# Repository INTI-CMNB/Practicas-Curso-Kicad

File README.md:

# Practicas-Curso-Kicad
Prácticas para el curso Introductorio de de Kicad dictado por INTI.

## Consigna
Cada participante del curso trabajará en un subdirectorio con su Apellido_Nombre, sin espacios, tildes, eñes o caracteres especiales.

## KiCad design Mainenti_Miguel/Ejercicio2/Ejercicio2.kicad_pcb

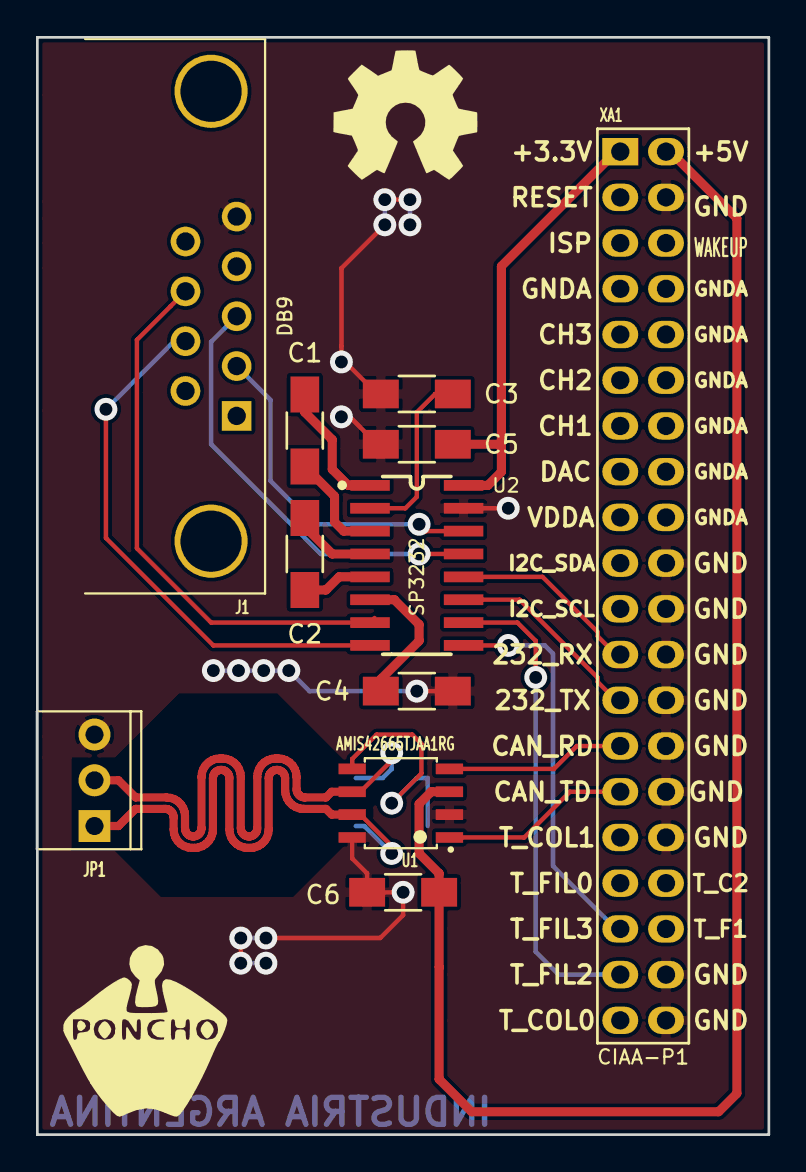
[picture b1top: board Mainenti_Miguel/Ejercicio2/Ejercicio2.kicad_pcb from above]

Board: 2 copper layers, 40.6 x 61.0 mm, 14 parts (0 on the bottom side), 22 nets.

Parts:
C1, C2, C3, C4, C5: 100nF; C_1206_Handsoldering
C6: C; C_1206_Handsoldering
G101: Logo_OSHWA
J1: DB9; DB9_F_TH
JP1: CONN_3; CON_PALETA_3
R1, R2: 60; R_1206_HandSoldering
U1: AMIS42665TJAA1RG; SOIC-8
U2: SP3232; SP3232ECN-SOIC16N
XA1: Conn_Poncho2P_2x_20x2; Conn_Poncho_Derecha

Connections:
+3.3V: C5.1, U2.16, XA1.1
+5V: C6.2, U1.3, XA1.2
/Conector y Can/CAN_N: JP1.2, R2.2, U1.6
/Conector y Can/CAN_P: JP1.1, R1.1, U1.7
/Conector y Can/CAN_RX: U1.4, XA1.27
/Conector y Can/CAN_TX: U1.1, XA1.29
/Conector y Can/CTS: U2.10, XA1.37
/Conector y Can/RTS: U2.9, XA1.35
/Conector y Can/RXD: U2.11, XA1.25
/Conector y Can/TXD: U2.12, XA1.23
GND: C3.1, C4.1, C5.2, C6.1, J1.5, JP1.3, U1.2, U1.8, U2.15, XA1.4, XA1.20, XA1.22, XA1.24, XA1.26, XA1.28, XA1.30, XA1.32, XA1.38, XA1.40
unnamed: C1.1, U2.1
unnamed: C1.2, U2.3
unnamed: C2.1, U2.4
unnamed: C2.2, U2.5
unnamed: C3.2, U2.2
unnamed: C4.2, U2.6
unnamed: J1.2, U2.14
unnamed: J1.3, U2.13
unnamed: J1.7, U2.8
unnamed: J1.8, U2.7
unnamed: R1.2, R2.1, U1.5

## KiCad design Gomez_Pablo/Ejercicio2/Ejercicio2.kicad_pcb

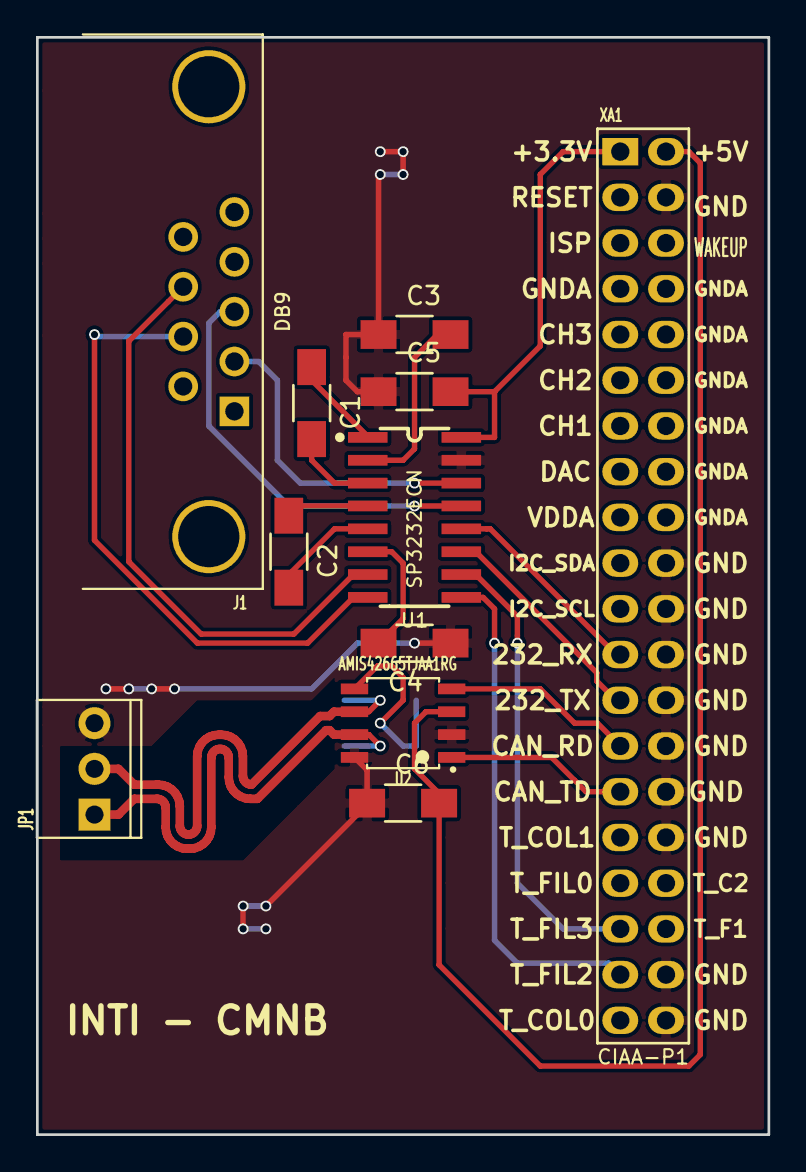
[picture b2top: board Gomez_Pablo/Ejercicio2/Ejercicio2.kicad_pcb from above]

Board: 2 copper layers, 40.6 x 61.0 mm, 13 parts (0 on the bottom side), 22 nets.

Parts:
C1, C2, C3, C4, C5: 100nF; C_1206_Handsoldering
C6: 100 nF; C_1206_Handsoldering
J1: DB9; DB9_F_TH
JP1: CAN; CON_PALETA_3
R1, R2: 60; R_1206_HandSoldering
U1: SP3232ECN; SP3232ECN-SOIC16N
U2: AMIS42665TJAA1RG; SOIC-8
XA1: Conn_Poncho2P_2x_20x2; Conn_Poncho_Derecha

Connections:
+3.3V: C5.2, U1.16, XA1.1
+5V: C6.2, U2.3, XA1.2
/Conector/CAN_N: JP1.2, R2.2, U2.6
/Conector/CAN_P: JP1.1, R1.1, U2.7
/Conector/CAN_RX: U2.4, XA1.27
/Conector/CAN_TX: U2.1, XA1.29
/Conector/CTS: U1.10, XA1.35
/Conector/RTS: U1.9, XA1.37
/Conector/RXD: U1.11, XA1.25
/Conector/TXD: U1.12, XA1.23
GND: C3.1, C4.1, C5.1, C6.1, JP1.3, U1.15, U2.2, U2.8, XA1.4, XA1.20, XA1.22, XA1.24, XA1.26, XA1.28, XA1.30, XA1.32, XA1.38, XA1.40
unnamed: C1.1, U1.1
unnamed: C1.2, U1.3
unnamed: C2.1, U1.4
unnamed: C2.2, U1.5
unnamed: C3.2, U1.2
unnamed: C4.2, U1.6
unnamed: J1.2, U1.14
unnamed: J1.3, U1.13
unnamed: J1.7, U1.8
unnamed: J1.8, U1.7
unnamed: R1.2, R2.1, U2.5

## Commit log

2015-11-18 Creo directorio.
2015-11-19 Edito el README.
2015-11-26 pruebas sobre lista.
2015-11-26 Agrego UVAS.
2015-11-26 Agrego GUINDA.
2015-11-26 Borro lista de compras.
2015-11-27 Agregados los archivos para los ejercicios 1 y 2.
2015-11-27 Muevo dir Diego_Brengi a Materiales
2015-11-27 Agregados los directorios de trabajo de los asistentes.
2015-12-01 Agrego presentación Día 2.
2015-12-01 se cambio en el id
2015-12-01 EHS Agrego Ejercicio1
2015-12-01 Agrego mi ejercicio1
2015-12-01 Agrego mi ejercicio1.
2015-12-01 Agrego ejercicio 1
2015-12-01 Agrego mi ejercicio 1
2015-12-01 NS: Agrego mi ejercicio 1
2015-12-01 Agrego mi ejercicio 1. DC
2015-12-01 Agrego mi ejercicio 1. PO
2015-12-01 Agrego mi ejercicio 1 SN.
2015-12-01 Ejercicio1
2015-12-01 Agrego ejercicio 1 1.0
2015-12-01 agrego el ejc1 version 1.0
2015-12-01 Agrego mi ejercicio 1.
2015-12-01 Agrego ej_1 ss
2015-12-01 ejercicio 1
2015-12-01 borrado
2015-12-01 Agrego Ej 1.
2015-12-01 Agrego ej. 1 final
2015-12-01 GoCu .Agrego ejercicio 1
2015-12-01 Borro carpeta vieja
2015-12-01 Añado nuevo directorio con Gerbers
2015-12-01 lista de ignorados
2015-12-01 Agrego gitignore
2015-12-01 inicio del proyecto 2
2015-12-01 subir gitignore
2015-12-01 adherido el ignore
2015-12-01 git ignore
2015-12-01 Agrego archivos a ignorar
2015-12-01 Se agrego .gitignore
2015-12-01 se sube gitignore
2015-12-01 Se agrega el archivo .gitignore
2015-12-01 add git ignore
2015-12-01 GoCu agrego el gitignore
2015-12-01 agregado ignore
2015-12-01 Agrego tabla RS232 DTE DCE.
2015-12-01 Agregado Ejercicio 2
2015-12-01 Realizado el Electrical Rule Check. Corregidos Errores Se agregó campo Digikey/Mouser en todos los componentes Se modificó Digikey/Mouser en U1 y U2
2015-12-01 Creado Netlist Realizado BOM con Scripts Python dentro de Kicad
2015-12-01 Added footprint library Assigned Foot-Symbol updated netlist and BOM
2015-12-01 Creado el Footprint 1206
2015-12-01 Cambiados footprints Revisando placement en PCB
2015-12-01 Agregado la presentación del día 1.
2015-12-02 mando archivos
2015-12-02 mi ejercicio2
2015-12-02 Minor changes on pcb
2015-12-02 ejercicio 2 pcb
2015-12-02 Se suben sólo los archivos recomendados
2015-12-02 GoCu subo el ruteo preliminar
2015-12-02 Se agregan los archivos opcionales
2015-12-02 Se sube Poncho_RS232_CAN_1.0.0
2015-12-02 Agrego archivos ej_2
2015-12-02 Agrego Ej2 solo ruteado sin planos
2015-12-02 Se agregan los directorios utilizados para el Ejercicio 2
2015-12-02 Agrego ej2 SN.
2015-12-02 agrego lo necesario
2015-12-02 change .gitignore
2015-12-02 GoCu modifico el gitignore
2015-12-02 Ejercicio 2
2015-12-02 Added GND planes
2015-12-02 Ejercicio 2 n
2015-12-02 Agrego .gitignore actualizado
2015-12-02 version 1 del poncho
2015-12-02 version 1 del poncho faltaba el conector.sch
2015-12-02 Faltan rutear GND
2015-12-02 Agrego los archivos del Ejercicio 2 con parte del PCB
2015-12-02 subo Ejercicio 2 1.1
2015-12-02 Agrego directorios del proyecto
2015-12-02 Subo Ejer2. PO
2015-12-02 sumado un archivo al gitignore
2015-12-02 actualizado
2015-12-02 Actualizo PCB
2015-12-02 agregadas leyendas, cutouts y keepouts
2015-12-02 Added 3D
2015-12-02 3D routing
2015-12-02 con 3d
2015-12-02 Agrego 3D
2015-12-02 Agrego 3d. PO
2015-12-02 Subo los 3d shapes
2015-12-02 Se sube la versión actualizada del pcb
2015-12-02 GoCu Agregado los planos y la vista 3D
2015-12-02 Se agregan los archivos pcb con 3d
2015-12-02 Se sube modelo 3d Poncho_RS232_CAN v1.0.0
2015-12-02 Version c/ modelos 3d
2015-12-02 se sube modificacion en pcb
2015-12-02 ruteado y con 3d
2015-12-02 Se sube 3dshapes
2015-12-02 Agregada Licencia
2015-12-02 Agrego licencia. PO
2015-12-02 licensia abierta
2015-12-02 Actualizo doc
2015-12-02 Agrego PCB ejercicio 2 con 3D SN
2015-12-02 se agregaron logos y licencia. Se activaron capas de cobre que estaban desactivadas
2015-12-02 plano de tierra y 3d
2015-12-02 Subo la licencia
2015-12-02 Se agrega modificacion de pcb y license
2015-12-02 modifico licencia
2015-12-02 nuevo componente
2015-12-02 Agrego componente multiparte. PO
2015-12-02 corregido
2015-12-02 se sube la librería modificada
2015-12-02 Se agrego libreria MP
2015-12-02 agrego libreria
2015-12-02 Actualizo carpeta libs
2015-12-02 Componente Multiparte
2015-12-02 IDEM
2015-12-02 se sube componente sp3232 multiparte
2015-12-02 agregado comp. multiparte
2015-12-02 GoCu Agregado el componente multipart
2015-12-02 agrego componente a ej2.lib
2015-12-02 change library
2015-12-02 lib mulitparte
2015-12-02 Agrego lib scp232 nueva esquematico SN
2015-12-02 Nuevo Footprint
2015-12-02 Agrego footprint smd 32 pines smd SN
2015-12-02 Se sube el footprint del QFN64 creado a partir del tutorial del CERN
2015-12-02 PCB Modo OpenGL
2015-12-02 Added Stack-UP
2015-12-02 Probada característica lenght tunning.
    Falló Kicad y no pude realizar el par diferencial
2015-12-02 Subo el diseño con pares dif
2015-12-02 placa final
2015-12-02 ruteo del par diferencial y ecualizado
2015-12-02 se ecualizan pares diferenciales
2015-12-02 agregado par dif
2015-12-02 Al pcb se le agregaron los controles de impedancias
2015-12-02 Agrego PCB par diferencial CAN
2015-12-02 par diferencial
2015-12-02 work finished
2015-12-02 Agrego el ruteo del CAN
2015-12-02 Version final
2015-12-03 Ordeno a los asistentes en un subdirectorio.
2015-12-03 Muevo a Ferraro Matías.
2015-12-03 Borro práctica demostrativa de Noelia.
2016-06-09 Agrego el material del curso CAPSE sobre KiCad y Ponchos.
2016-06-14 Agrego materiales para el ejercicio 2 versión CESE.
2016-06-24 Corrijo algunos títulos de la presentación de Ponchos, Clase2.
2016-08-11 Agrego bibliotecas para el ejercicio de rele2x del Workshop del SASE2016.
